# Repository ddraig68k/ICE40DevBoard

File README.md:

# Lattice ICE40HX8K Development board

Intended as a development system for a software CPU computer design.

Includes:
16-bit VGA video
Audio output
512KB SRAM
FT232H interface for UART and device programming
MicroSD card
PS/2 Keyboard and mouse
Sega Megadrive joystick interface
3 push buttons
3 user LEDs
2 seven segment LEDs

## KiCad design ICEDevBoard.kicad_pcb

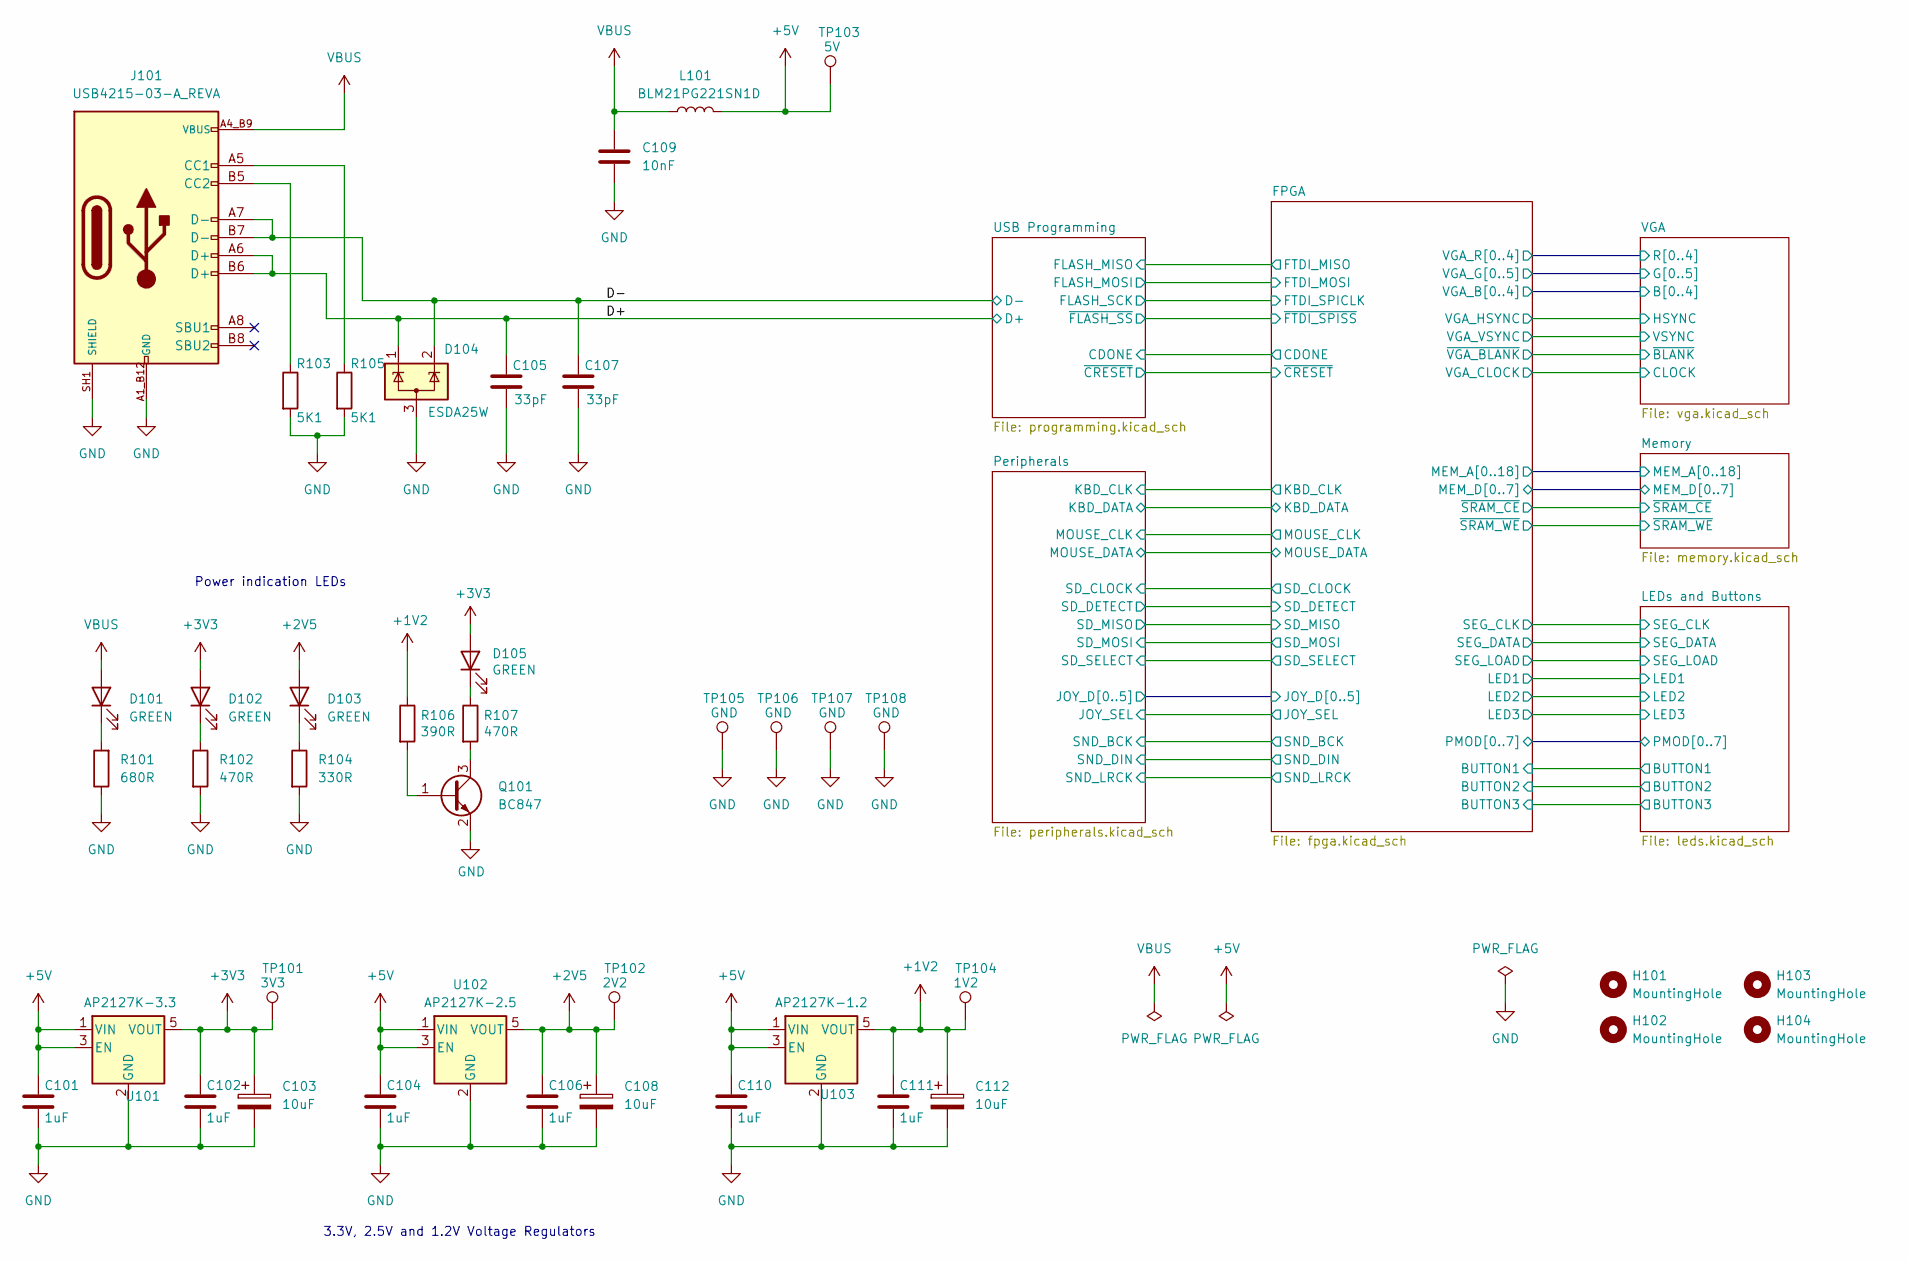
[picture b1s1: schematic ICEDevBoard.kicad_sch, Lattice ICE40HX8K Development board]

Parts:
C101, C102, C104, C106, C110, C111: 1uF; C_0805_2012Metric
C103, C108, C112: 10uF; CP_Elec_4x5.3
C105, C107: 33pF; C_0805_2012Metric
C109: 10nF; C_0805_2012Metric
D101, D102, D103, D105: GREEN; LED_1206_3216Metric
D104: ESDA25W; SOT-23-3
H101, H102, H103, H104: MountingHole; MountingHole_4.3mm_M4
J101: USB4215-03-A_REVA; GCT_USB4215-03-A_REVA; PARTREV A
L101: BLM21PG221SN1D; L_1206_3216Metric
Q101: BC847; SOT-23
R101: 680R; R_0805_2012Metric
R102, R107: 470R; R_0805_2012Metric
R103, R105: 5K1; R_0805_2012Metric
R104: 330R; R_0805_2012Metric
R106: 390R; R_0805_2012Metric
TP101: 3V3; TestPoint_Pad_D1.0mm
TP102: 2V2; TestPoint_Pad_D1.0mm
TP103: 5V; TestPoint_Pad_D1.0mm
TP104: 1V2; TestPoint_Pad_D1.0mm
TP105, TP106, TP107, TP108: GND; TestPoint_THTPad_D1.0mm_Drill0.5mm
U101: AP2127K-3.3; SOT-23-5
U102: AP2127K-2.5; SOT-23-5
U103: AP2127K-1.2; SOT-23-5

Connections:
+1V2: C111.1, C112.1, R106.1, TP104.1, U103.5 (VOUT); also elsewhere on the board
+2V5: C106.1, C108.1, D103.2 (A), TP102.1, U102.5 (VOUT); also elsewhere on the board
+3V3: C102.1, C103.1, D102.2 (A), D105.2 (A), TP101.1, U101.5 (VOUT); also elsewhere on the board
+5V: C101.1, C104.1, C110.1, L101.2, TP103.1, U101.1 (VIN), U101.3 (EN), U102.1 (VIN), U102.3 (EN), U103.1 (VIN), U103.3 (EN); also elsewhere on the board
/D+: C105.1, D104.1 (K), J101.A6 (D+), J101.B6 (D+); also elsewhere on the board
/D-: C107.1, D104.2 (K), J101.A7 (D-), J101.B7 (D-); also elsewhere on the board
GND: C101.2, C102.2, C103.2, C104.2, C105.2, C106.2, C107.2, C108.2, C109.2, C110.2, C111.2, C112.2, D104.3 (A), J101.A1_B12 (GND), J101.B1_A12 (GND), J101.SH1 (SHIELD), J101.SH2 (SHIELD), J101.SH3 (SHIELD), J101.SH4 (SHIELD), Q101.2 (E), R101.1, R102.2, R103.2, R104.2, R105.2, TP105.1, TP106.1, TP107.1, TP108.1, U101.2 (GND), U102.2 (GND), U103.2 (GND); also elsewhere on the board
unnamed: D101.1 (K), R101.2
unnamed: D102.1 (K), R102.1
unnamed: D103.1 (K), R104.1
unnamed: D105.1 (K), R107.1
unnamed: J101.A5 (CC1), R105.1
unnamed: J101.B5 (CC2), R103.1
unnamed: Q101.1 (B), R106.2
unnamed: Q101.3 (C), R107.2
VBUS: C109.1, D101.2 (A), J101.A4_B9 (VBUS), J101.B4_A9 (VBUS), L101.1

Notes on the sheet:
Power indication LEDs
3.3V, 2.5V and 1.2V Voltage Regulators

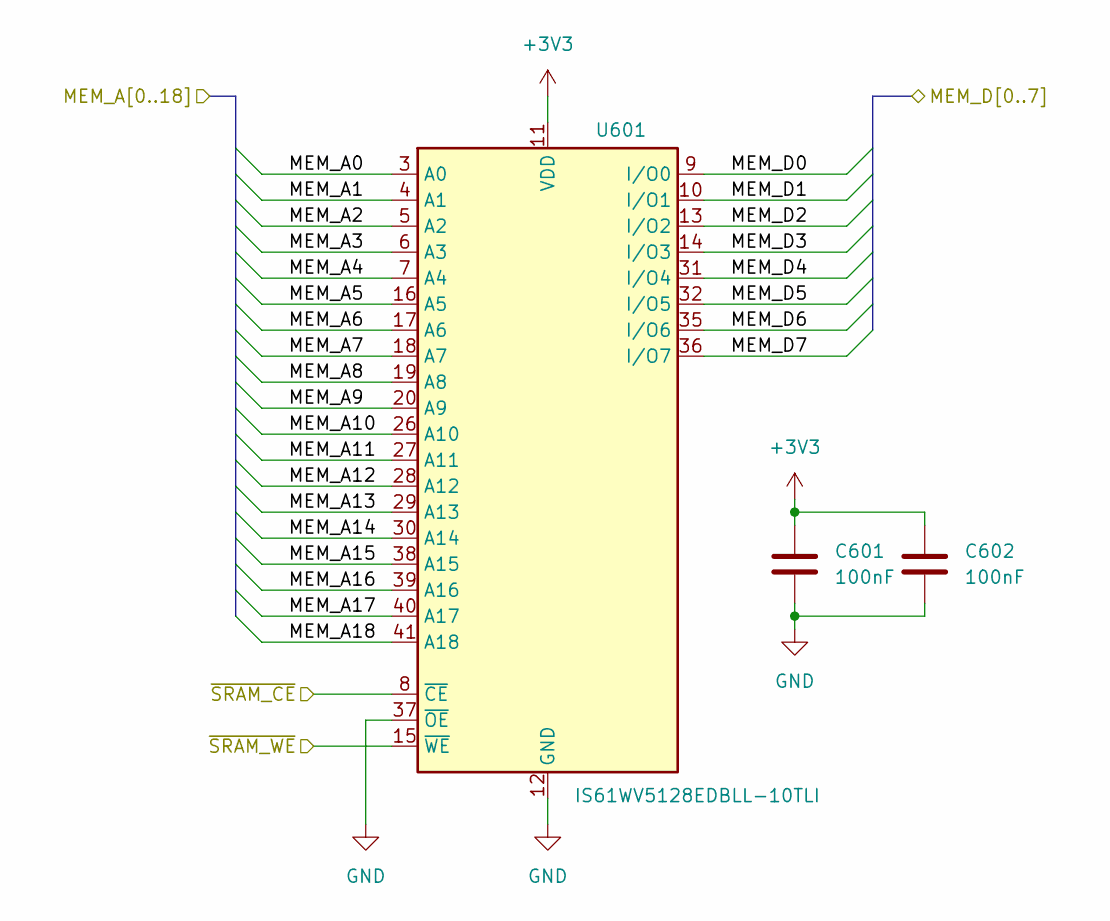
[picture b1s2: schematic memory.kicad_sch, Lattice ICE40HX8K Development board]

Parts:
C601, C602: 100nF; C_0805_2012Metric
U601: IS61WV5128EDBLL-10TLI; TSOP-II-44_10.16x18.41mm_P0.8mm

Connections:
+3V3: C601.1, C602.1, U601.11 (VDD), U601.33 (VDD); also elsewhere on the board
/FPGA/MEM_A0: U601.3 (A0); also elsewhere on the board
/FPGA/MEM_A1: U601.4 (A1); also elsewhere on the board
/FPGA/MEM_A2: U601.5 (A2); also elsewhere on the board
/FPGA/MEM_A3: U601.6 (A3); also elsewhere on the board
/FPGA/MEM_A4: U601.7 (A4); also elsewhere on the board
/FPGA/MEM_A5: U601.16 (A5); also elsewhere on the board
/FPGA/MEM_A6: U601.17 (A6); also elsewhere on the board
/FPGA/MEM_A7: U601.18 (A7); also elsewhere on the board
/FPGA/MEM_A8: U601.19 (A8); also elsewhere on the board
/FPGA/MEM_A9: U601.20 (A9); also elsewhere on the board
/FPGA/MEM_A10: U601.26 (A10); also elsewhere on the board
/FPGA/MEM_A11: U601.27 (A11); also elsewhere on the board
/FPGA/MEM_A12: U601.28 (A12); also elsewhere on the board
/FPGA/MEM_A13: U601.29 (A13); also elsewhere on the board
/FPGA/MEM_A14: U601.30 (A14); also elsewhere on the board
/FPGA/MEM_A15: U601.38 (A15); also elsewhere on the board
/FPGA/MEM_A16: U601.39 (A16); also elsewhere on the board
/FPGA/MEM_A17: U601.40 (A17); also elsewhere on the board
/FPGA/MEM_A18: U601.41 (A18); also elsewhere on the board
/FPGA/MEM_D0: U601.9 (I/O0); also elsewhere on the board
/FPGA/MEM_D1: U601.10 (I/O1); also elsewhere on the board
/FPGA/MEM_D2: U601.13 (I/O2); also elsewhere on the board
/FPGA/MEM_D3: U601.14 (I/O3); also elsewhere on the board
/FPGA/MEM_D4: U601.31 (I/O4); also elsewhere on the board
/FPGA/MEM_D5: U601.32 (I/O5); also elsewhere on the board
/FPGA/MEM_D6: U601.35 (I/O6); also elsewhere on the board
/FPGA/MEM_D7: U601.36 (I/O7); also elsewhere on the board
/FPGA/~SRAM_CE: U601.8 (~CE); also elsewhere on the board
/FPGA/~SRAM_WE: U601.15 (~WE); also elsewhere on the board
GND: C601.2, C602.2, U601.12 (GND), U601.34 (GND), U601.37 (~OE); also elsewhere on the board

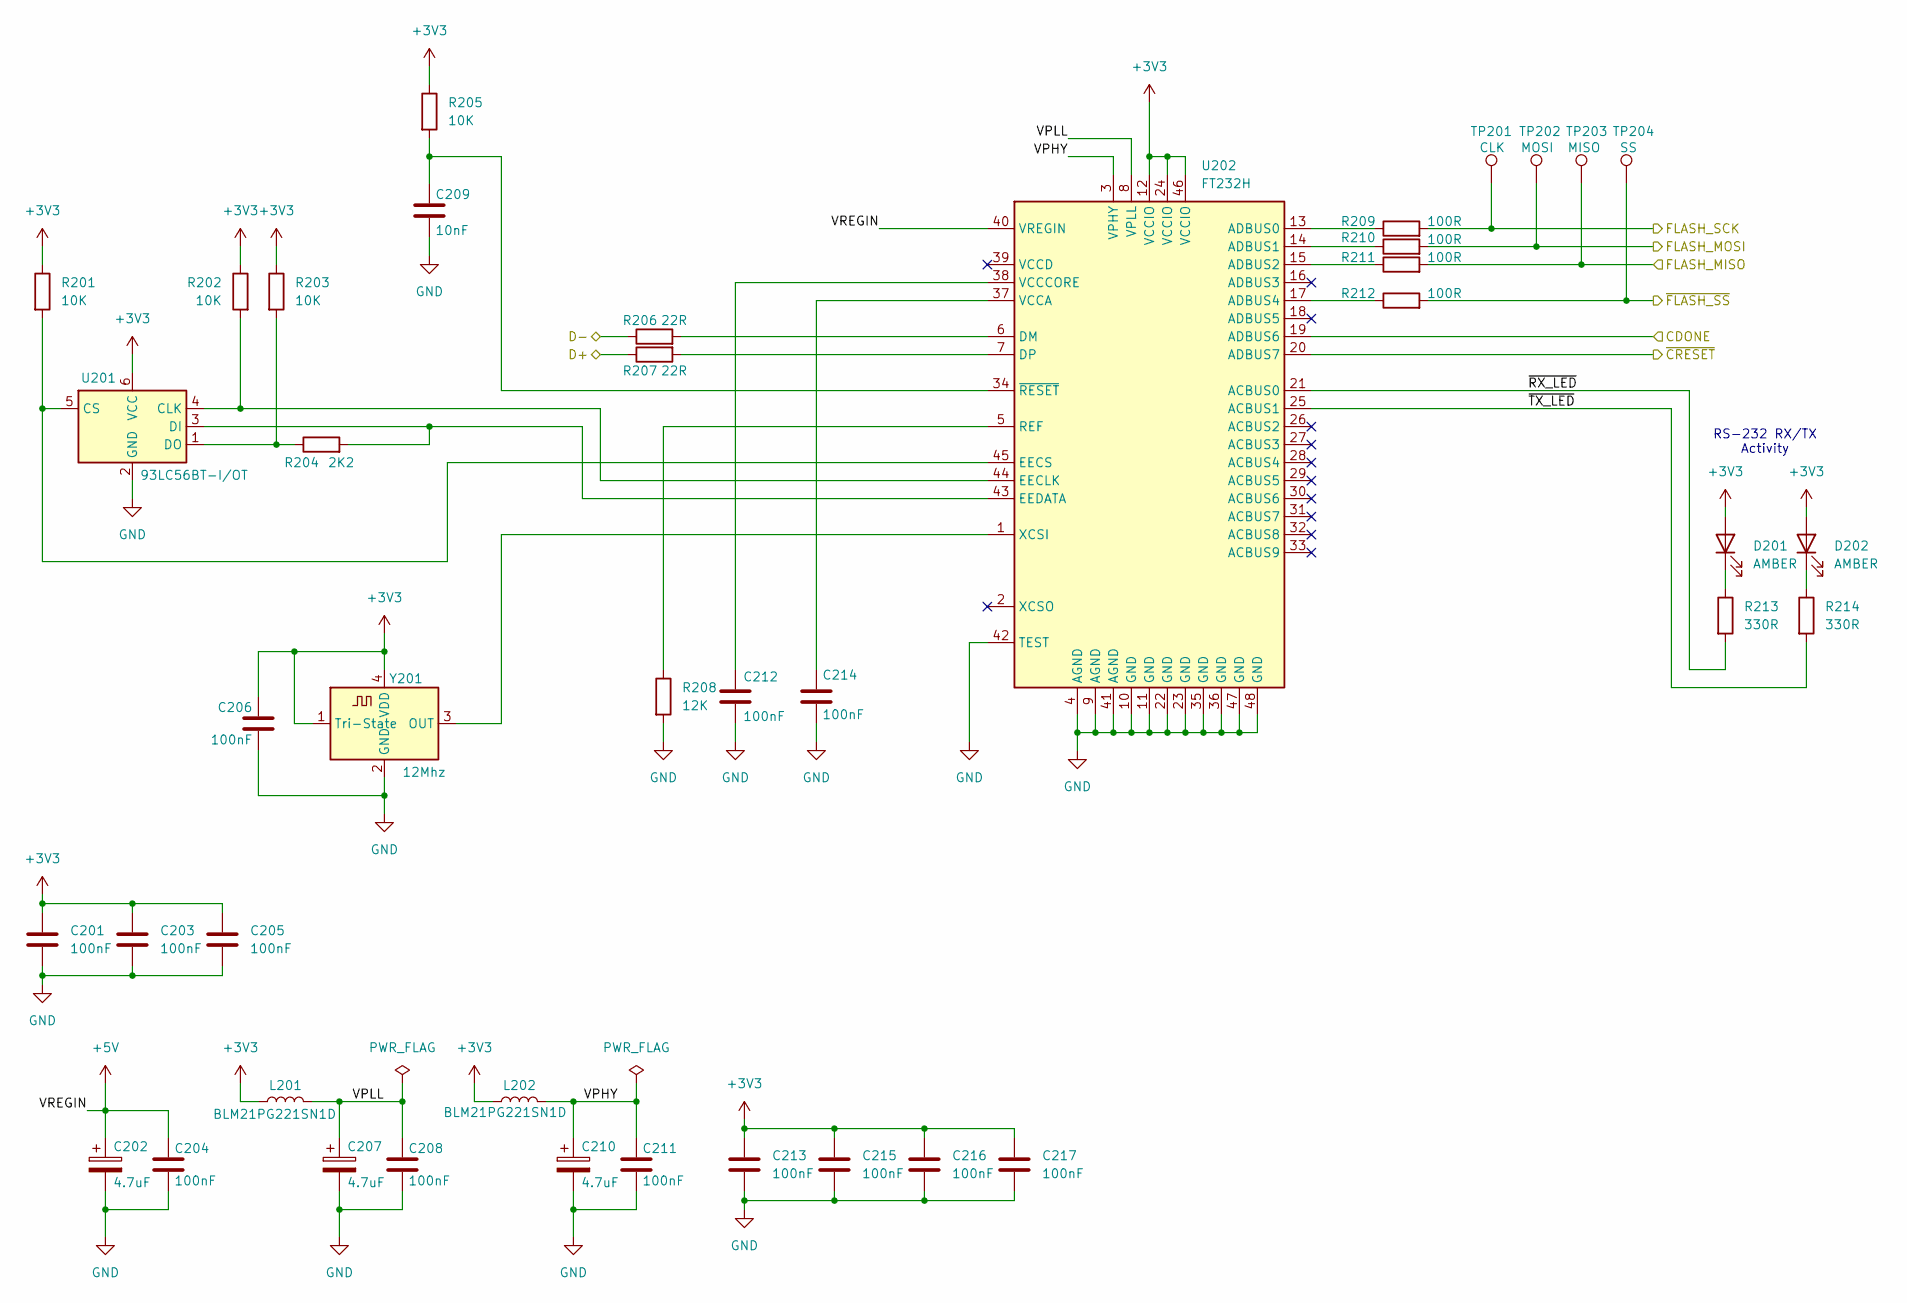
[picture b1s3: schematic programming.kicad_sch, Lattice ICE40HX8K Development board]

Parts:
C201, C203, C204, C205, C206, C208, C211, C212, C213, C214, C215, C216, C217: 100nF; C_0805_2012Metric
C202, C207, C210: 4.7uF; CP_Elec_4x5.3
C209: 10nF; C_0805_2012Metric
D201, D202: AMBER; LED_1206_3216Metric
L201, L202: BLM21PG221SN1D; L_1206_3216Metric
R201, R202, R203, R205: 10K; R_0805_2012Metric
R204: 2K2; R_0805_2012Metric
R206, R207: 22R; R_0805_2012Metric
R208: 12K; R_0805_2012Metric
R209, R210, R211, R212: 100R; R_0805_2012Metric
R213, R214: 330R; R_0805_2012Metric
TP201: CLK; TestPoint_Pad_D1.0mm
TP202: MOSI; TestPoint_Pad_D1.0mm
TP203: MISO; TestPoint_Pad_D1.0mm
TP204: SS; TestPoint_Pad_D1.0mm
U201: 93LC56BT-I/OT; SOT-23-6
U202: FT232H; LQFP-48_7x7mm_P0.5mm
Y201: 12Mhz; Oscillator_SMD_ECS_2520MV-xxx-xx-4Pin_2.5x2.0mm

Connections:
+3V3: C201.1, C203.1, C205.1, C206.1, C213.1, C215.1, C216.1, C217.1, D201.2 (A), D202.2 (A), L201.1, L202.1, R201.1, R202.1, R203.1, R205.1, U201.6 (VCC), U202.12 (VCCIO), U202.24 (VCCIO), U202.46 (VCCIO), Y201.1 (Tri-State), Y201.4 (VDD); also elsewhere on the board
+5V: C202.1, C204.1, U202.40 (VREGIN); also elsewhere on the board
/D+: R207.1; also elsewhere on the board
/D-: R206.1; also elsewhere on the board
/FPGA/CDONE: U202.19 (ADBUS6); also elsewhere on the board
/FPGA/FTDI_MISO: R211.2, TP203.1; also elsewhere on the board
/FPGA/FTDI_MOSI: R210.2, TP202.1; also elsewhere on the board
/FPGA/FTDI_SPICLK: R209.2, TP201.1; also elsewhere on the board
/FPGA/~CRESET: U202.20 (ADBUS7); also elsewhere on the board
/FPGA/~FTDI_SPISS: R212.2, TP204.1; also elsewhere on the board
/USB Programming/VPHY: C210.1, C211.1, L202.2, U202.3 (VPHY)
/USB Programming/VPLL: C207.1, C208.1, L201.2, U202.8 (VPLL)
/USB Programming/~RX_LED: R213.2, U202.21 (ACBUS0)
/USB Programming/~TX_LED: R214.2, U202.25 (ACBUS1)
GND: C201.2, C202.2, C203.2, C204.2, C205.2, C206.2, C207.2, C208.2, C209.2, C210.2, C211.2, C212.2, C213.2, C214.2, C215.2, C216.2, C217.2, R208.2, U201.2 (GND), U202.4 (AGND), U202.9 (AGND), U202.10 (GND), U202.11 (GND), U202.22 (GND), U202.23 (GND), U202.35 (GND), U202.36 (GND), U202.41 (AGND), U202.42 (TEST), U202.47 (GND), U202.48 (GND), Y201.2 (GND); also elsewhere on the board
unnamed: D201.1 (K), R213.1
unnamed: D202.1 (K), R214.1
unnamed: R202.2, U201.4 (CLK), U202.44 (EECLK)
unnamed: R201.2, U201.5 (CS), U202.45 (EECS)
unnamed: R204.2, U201.3 (DI), U202.43 (EEDATA)
unnamed: R203.2, R204.1, U201.1 (DO)
unnamed: R209.1, U202.13 (ADBUS0)
unnamed: R210.1, U202.14 (ADBUS1)
unnamed: R211.1, U202.15 (ADBUS2)
unnamed: R212.1, U202.17 (ADBUS4)
unnamed: R206.2, U202.6 (DM)
unnamed: R207.2, U202.7 (DP)
unnamed: R208.1, U202.5 (REF)
unnamed: C214.1, U202.37 (VCCA)
unnamed: C212.1, U202.38 (VCCCORE)
unnamed: U202.1 (XCSI), Y201.3 (OUT)
unnamed: C209.1, R205.2, U202.34 (~RESET)

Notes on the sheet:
RS-232 RX/TX Activity

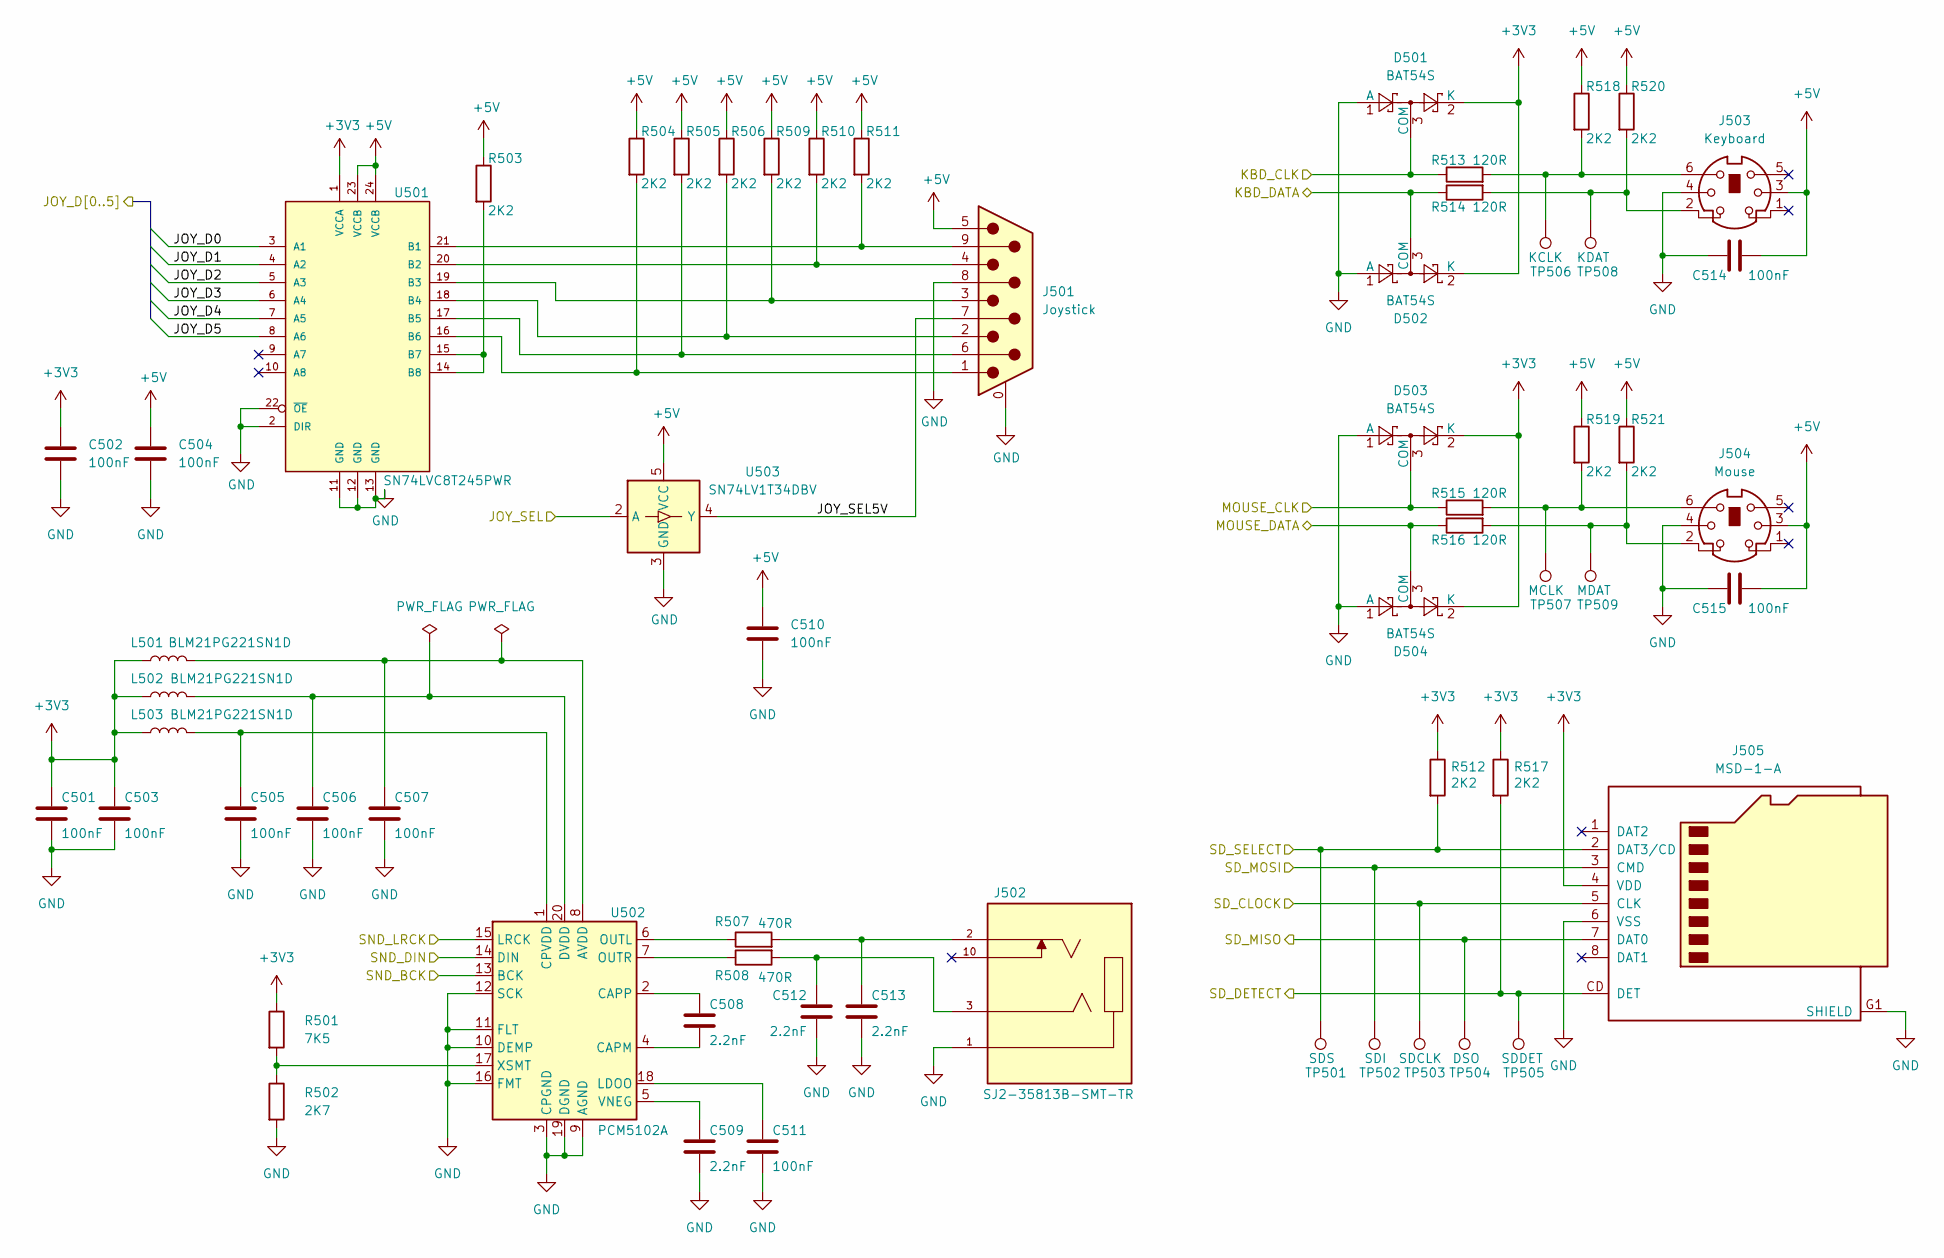
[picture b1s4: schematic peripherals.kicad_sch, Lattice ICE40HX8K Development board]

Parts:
C501, C502, C503, C504, C505, C506, C507, C510, C511, C514, C515: 100nF; C_0805_2012Metric
C508, C509, C512, C513: 2.2nF; C_0805_2012Metric
D501, D502, D503, D504: BAT54S; SOT-23
J501: Joystick; DSUB-9_Pins_Horizontal_P2.77x2.84mm_EdgePinOffset4.94mm_Hou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
J502: SJ2-35813B-SMT-TR; CUI_SJ2-35813B-SMT-TR
J503: Keyboard; MINI-DIN-6-FULL-SHIELD
J504: Mouse; MINI-DIN-6-FULL-SHIELD
J505: MSD-1-A; CUI_MSD-1-A
L501, L502, L503: BLM21PG221SN1D; L_1206_3216Metric
R501: 7K5; R_0805_2012Metric
R502: 2K7; R_0805_2012Metric
R503, R504, R505, R506, R509, R510, R511, R512, R517, R518, R519, R520, R521: 2K2; R_0805_2012Metric
R507, R508: 470R; R_0805_2012Metric
R513, R514, R515, R516: 120R; R_0805_2012Metric
TP501: SDS; TestPoint_Pad_D1.0mm
TP502: SDI; TestPoint_Pad_D1.0mm
TP503: SDCLK; TestPoint_Pad_D1.0mm
TP504: DSO; TestPoint_Pad_D1.0mm
TP505: SDDET; TestPoint_Pad_D1.0mm
TP506: KCLK; TestPoint_Pad_D1.0mm
TP507: MCLK; TestPoint_Pad_D1.0mm
TP508: KDAT; TestPoint_Pad_D1.0mm
TP509: MDAT; TestPoint_Pad_D1.0mm
U501: SN74LVC8T245PWR; SOP65P640X120-24N
U502: PCM5102A; TSSOP-20_4.4x6.5mm_P0.65mm
U503: SN74LV1T34DBV; SOT-23-5

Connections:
+3V3: C501.1, C502.1, C503.1, D501.2 (K), D502.2 (K), D503.2 (K), D504.2 (K), J505.4 (VDD), L501.1, L502.1, L503.1, R501.1, R512.1, R517.1, U501.1 (VCCA); also elsewhere on the board
+5V: C504.1, C510.1, C514.2, C515.2, J501.5, J503.3, J504.3, R503.1, R504.1, R505.1, R506.1, R509.1, R510.1, R511.1, R518.1, R519.1, R520.1, R521.1, U501.23 (VCCB), U501.24 (VCCB), U503.5 (VCC); also elsewhere on the board
/FPGA/JOY_D0: U501.3 (A1); also elsewhere on the board
/FPGA/JOY_D1: U501.4 (A2); also elsewhere on the board
/FPGA/JOY_D2: U501.5 (A3); also elsewhere on the board
/FPGA/JOY_D3: U501.6 (A4); also elsewhere on the board
/FPGA/JOY_D4: U501.7 (A5); also elsewhere on the board
/FPGA/JOY_D5: U501.8 (A6); also elsewhere on the board
/FPGA/JOY_SEL: U503.2 (A); also elsewhere on the board
/FPGA/KBD_CLK: D501.3 (COM), R513.1; also elsewhere on the board
/FPGA/KBD_DATA: D502.3 (COM), R514.1; also elsewhere on the board
/FPGA/MOUSE_CLK: D503.3 (COM), R515.1; also elsewhere on the board
/FPGA/MOUSE_DATA: D504.3 (COM), R516.1; also elsewhere on the board
/FPGA/SD_CLOCK: J505.5 (CLK), TP503.1; also elsewhere on the board
/FPGA/SD_DETECT: J505.CD (DET), R517.2, TP505.1; also elsewhere on the board
/FPGA/SD_MISO: J505.7 (DAT0), TP504.1; also elsewhere on the board
/FPGA/SD_MOSI: J505.3 (CMD), TP502.1; also elsewhere on the board
/FPGA/SD_SELECT: J505.2 (DAT3/CD), R512.2, TP501.1; also elsewhere on the board
/FPGA/SND_BCK: U502.13 (BCK); also elsewhere on the board
/FPGA/SND_DIN: U502.14 (DIN); also elsewhere on the board
/FPGA/SND_LRCK: U502.15 (LRCK); also elsewhere on the board
/Peripherals/JOY_SEL5V: J501.7, U503.4 (Y)
GND: C501.2, C502.2, C503.2, C504.2, C505.2, C506.2, C507.2, C509.2, C510.2, C511.2, C512.2, C513.2, C514.1, C515.1, D501.1 (A), D502.1 (A), D503.1 (A), D504.1 (A), J501.0 (PAD), J501.8, J502.1, J503.4, J504.4, J505.6 (VSS), J505.G1 (SHIELD), J505.G2 (SHIELD), J505.G3 (SHIELD), J505.G4 (SHIELD), R502.2, U501.2 (DIR), U501.11 (GND), U501.12 (GND), U501.13 (GND), U501.22 (~OE), U502.3 (CPGND), U502.9 (AGND), U502.10 (DEMP), U502.11 (FLT), U502.12 (SCK), U502.16 (FMT), U502.19 (DGND), U503.3 (GND); also elsewhere on the board
unnamed: C512.1, J502.3, R508.2
unnamed: C513.1, J502.2, R507.2
unnamed: J503.2, R514.2, R520.2, TP508.1
unnamed: J503.6, R513.2, R518.2, TP506.1
unnamed: J504.2, R516.2, R521.2, TP509.1
unnamed: J504.6, R515.2, R519.2, TP507.1
unnamed: J501.9, R511.2, U501.21 (B1)
unnamed: J501.4, R510.2, U501.20 (B2)
unnamed: J501.3, R509.2, U501.19 (B3)
unnamed: J501.2, R506.2, U501.18 (B4)
unnamed: J501.6, R505.2, U501.17 (B5)
unnamed: J501.1, R504.2, U501.16 (B6)
unnamed: R503.2, U501.14 (B8), U501.15 (B7)
unnamed: C507.1, L501.2, U502.8 (AVDD)
unnamed: C508.2, U502.4 (CAPM)
unnamed: C508.1, U502.2 (CAPP)
unnamed: C505.1, L503.2, U502.1 (CPVDD)
unnamed: C506.1, L502.2, U502.20 (DVDD)
unnamed: C511.1, U502.18 (LDOO)
unnamed: R507.1, U502.6 (OUTL)
unnamed: R508.1, U502.7 (OUTR)
unnamed: C509.1, U502.5 (VNEG)
unnamed: R501.2, R502.1, U502.17 (XSMT)

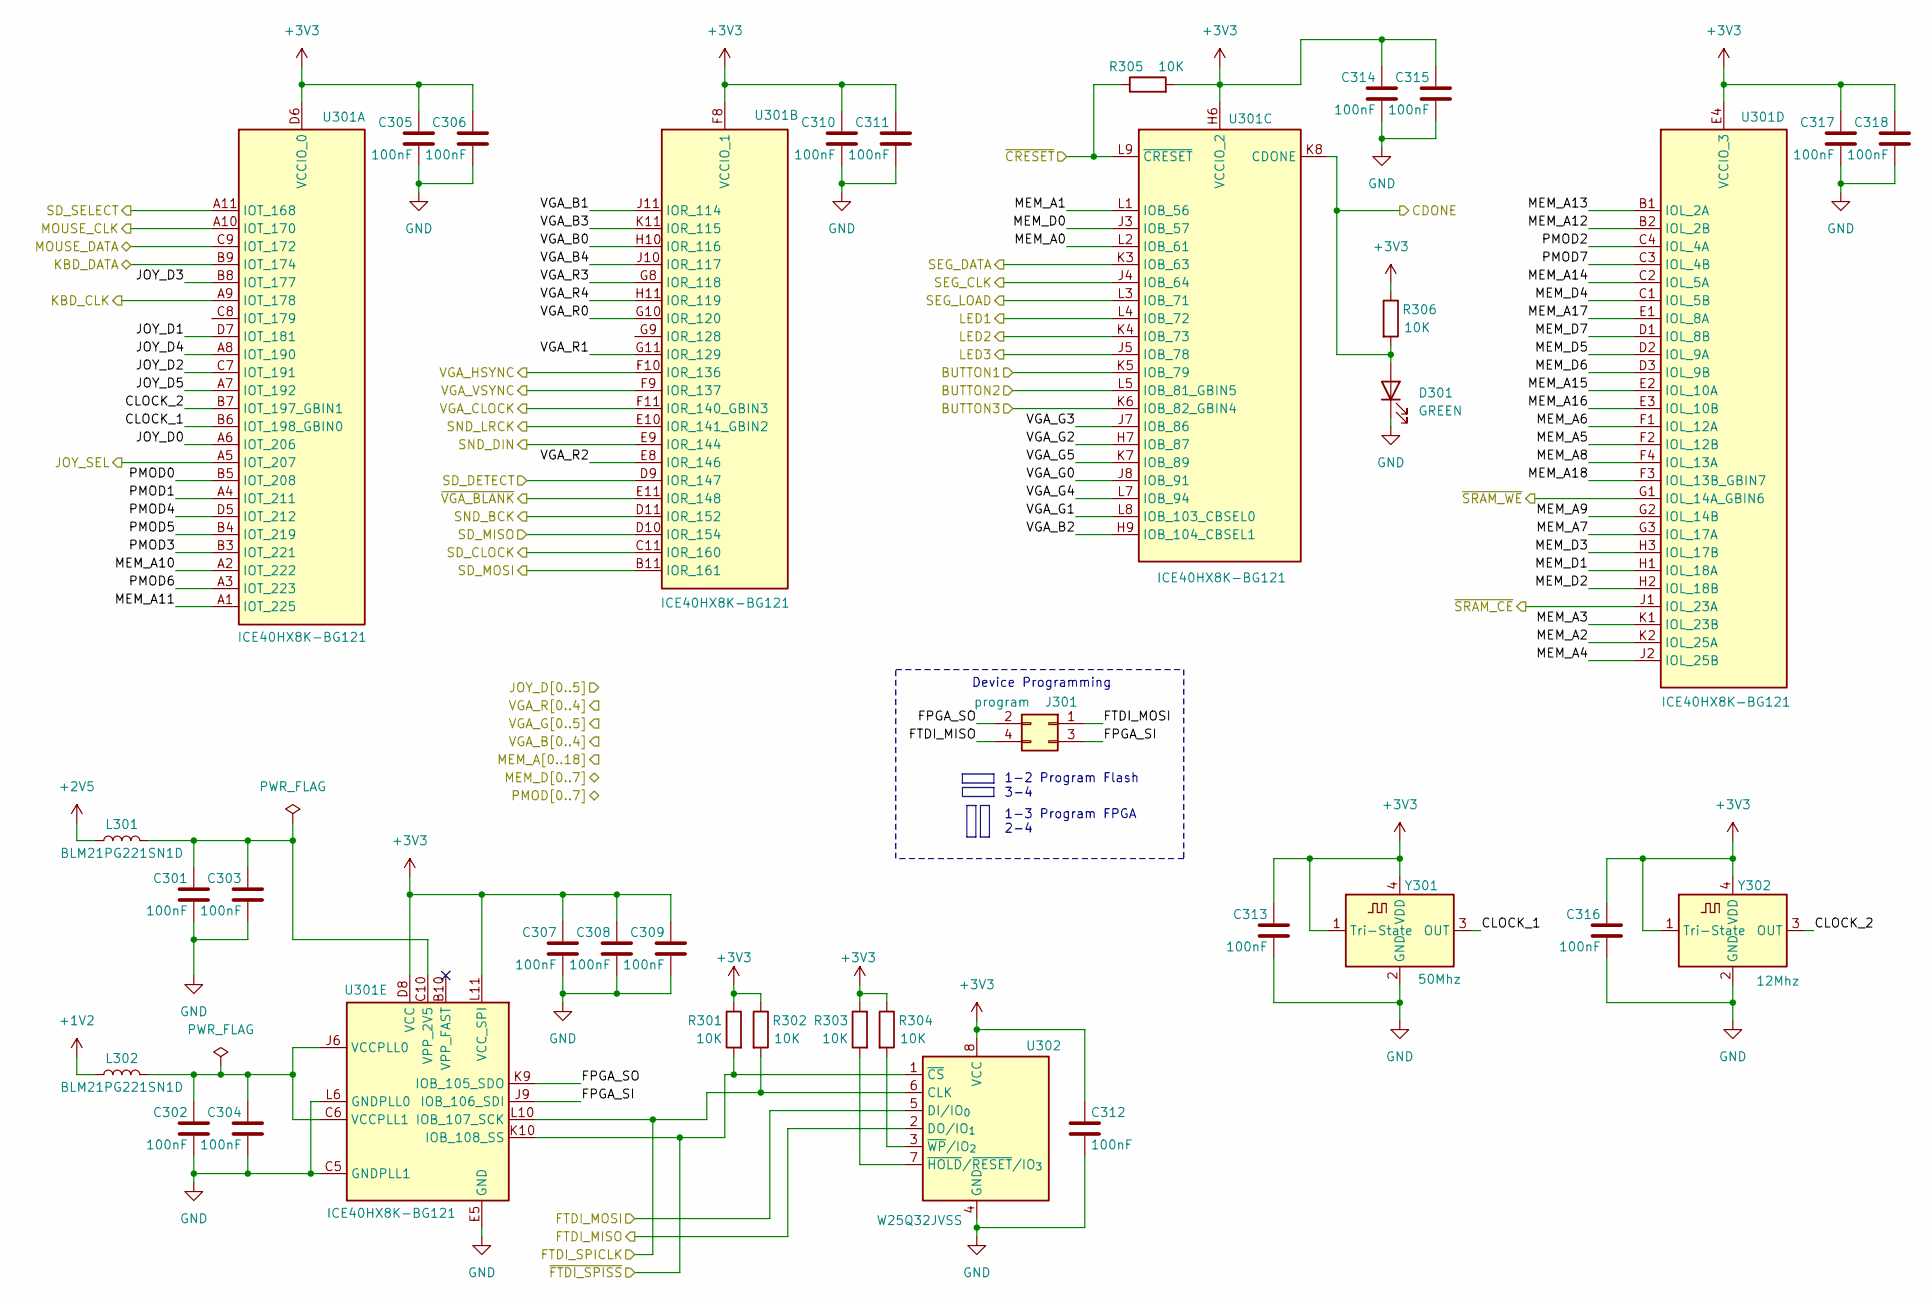
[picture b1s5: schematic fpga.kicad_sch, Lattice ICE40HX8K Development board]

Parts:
C301, C302, C303, C304, C305, C306, C307, C308, C309, C310, C311, C312, C313, C314, C315, C316, C317, C318: 100nF; C_0603_1608Metric
D301: GREEN; LED_1206_3216Metric
J301: program; PinSocket_2x02_P2.54mm_Vertical
L301, L302: BLM21PG221SN1D; L_1206_3216Metric
R301, R302, R303, R304, R305, R306: 10K; R_0805_2012Metric
U301: ICE40HX8K-BG121; BGA-121_9.0x9.0mm_Layout11x11_P0.8mm_Ball0.4mm_Pad0.35mm_NS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
U302: W25Q32JVSS; SOIC-8_5.3x5.3mm_P1.27mm
Y301: 50Mhz; Oscillator_SMD_ECS_2520MV-xxx-xx-4Pin_2.5x2.0mm
Y302: 12Mhz; Oscillator_SMD_ECS_2520MV-xxx-xx-4Pin_2.5x2.0mm

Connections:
+1V2: L302.1; also elsewhere on the board
+2V5: L301.1; also elsewhere on the board
+3V3: C305.1, C306.1, C307.1, C308.1, C309.1, C310.1, C311.1, C312.1, C313.1, C314.1, C315.1, C316.1, C317.1, C318.1, R301.1, R302.1, R303.1, R304.1, R305.2, R306.1, U301.D4 (VCC), U301.D6 (VCCIO_0), U301.D8 (VCC), U301.E4 (VCCIO_3), U301.F8 (VCCIO_1), U301.G4 (VCCIO_3), U301.H4 (VCC), U301.H6 (VCCIO_2), U301.H8 (VCC), U301.L11 (VCC_SPI), U302.8 (VCC), Y301.1 (Tri-State), Y301.4 (VDD), Y302.1 (Tri-State), Y302.4 (VDD); also elsewhere on the board
/FPGA/BUTTON1: U301.K5 (IOB_79); also elsewhere on the board
/FPGA/BUTTON2: U301.L5 (IOB_81_GBIN5); also elsewhere on the board
/FPGA/BUTTON3: U301.K6 (IOB_82_GBIN4); also elsewhere on the board
/FPGA/CDONE: D301.2 (A), R306.2, U301.K8 (CDONE); also elsewhere on the board
/FPGA/CLOCK_1: U301.B6 (IOT_198_GBIN0), Y301.3 (OUT)
/FPGA/CLOCK_2: U301.B7 (IOT_197_GBIN1), Y302.3 (OUT)
/FPGA/FPGA_SI: J301.3, U301.J9 (IOB_106_SDI)
/FPGA/FPGA_SO: J301.2, U301.K9 (IOB_105_SDO)
/FPGA/FTDI_MISO: J301.4, U302.2 (DO/IO_{1}); also elsewhere on the board
/FPGA/FTDI_MOSI: J301.1, U302.5 (DI/IO_{0}); also elsewhere on the board
/FPGA/FTDI_SPICLK: R302.2, U301.L10 (IOB_107_SCK), U302.6 (CLK); also elsewhere on the board
/FPGA/JOY_D0: U301.A6 (IOT_206); also elsewhere on the board
/FPGA/JOY_D1: U301.D7 (IOT_181); also elsewhere on the board
/FPGA/JOY_D2: U301.C7 (IOT_191); also elsewhere on the board
/FPGA/JOY_D3: U301.B8 (IOT_177); also elsewhere on the board
/FPGA/JOY_D4: U301.A8 (IOT_190); also elsewhere on the board
/FPGA/JOY_D5: U301.A7 (IOT_192); also elsewhere on the board
/FPGA/JOY_SEL: U301.A5 (IOT_207); also elsewhere on the board
/FPGA/KBD_CLK: U301.A9 (IOT_178); also elsewhere on the board
/FPGA/KBD_DATA: U301.B9 (IOT_174); also elsewhere on the board
/FPGA/LED1: U301.L4 (IOB_72); also elsewhere on the board
/FPGA/LED2: U301.K4 (IOB_73); also elsewhere on the board
/FPGA/LED3: U301.J5 (IOB_78); also elsewhere on the board
/FPGA/MEM_A0: U301.L2 (IOB_61); also elsewhere on the board
/FPGA/MEM_A1: U301.L1 (IOB_56); also elsewhere on the board
/FPGA/MEM_A2: U301.K2 (IOL_25A); also elsewhere on the board
/FPGA/MEM_A3: U301.K1 (IOL_23B); also elsewhere on the board
/FPGA/MEM_A4: U301.J2 (IOL_25B); also elsewhere on the board
/FPGA/MEM_A5: U301.F2 (IOL_12B); also elsewhere on the board
/FPGA/MEM_A6: U301.F1 (IOL_12A); also elsewhere on the board
/FPGA/MEM_A7: U301.G3 (IOL_17A); also elsewhere on the board
/FPGA/MEM_A8: U301.F4 (IOL_13A); also elsewhere on the board
/FPGA/MEM_A9: U301.G2 (IOL_14B); also elsewhere on the board
/FPGA/MEM_A10: U301.A2 (IOT_222); also elsewhere on the board
/FPGA/MEM_A11: U301.A1 (IOT_225); also elsewhere on the board
/FPGA/MEM_A12: U301.B2 (IOL_2B); also elsewhere on the board
/FPGA/MEM_A13: U301.B1 (IOL_2A); also elsewhere on the board
/FPGA/MEM_A14: U301.C2 (IOL_5A); also elsewhere on the board
/FPGA/MEM_A15: U301.E2 (IOL_10A); also elsewhere on the board
/FPGA/MEM_A16: U301.E3 (IOL_10B); also elsewhere on the board
/FPGA/MEM_A17: U301.E1 (IOL_8A); also elsewhere on the board
/FPGA/MEM_A18: U301.F3 (IOL_13B_GBIN7); also elsewhere on the board
/FPGA/MEM_D0: U301.J3 (IOB_57); also elsewhere on the board
/FPGA/MEM_D1: U301.H1 (IOL_18A); also elsewhere on the board
/FPGA/MEM_D2: U301.H2 (IOL_18B); also elsewhere on the board
/FPGA/MEM_D3: U301.H3 (IOL_17B); also elsewhere on the board
/FPGA/MEM_D4: U301.C1 (IOL_5B); also elsewhere on the board
/FPGA/MEM_D5: U301.D2 (IOL_9A); also elsewhere on the board
/FPGA/MEM_D6: U301.D3 (IOL_9B); also elsewhere on the board
/FPGA/MEM_D7: U301.D1 (IOL_8B); also elsewhere on the board
/FPGA/MOUSE_CLK: U301.A10 (IOT_170); also elsewhere on the board
/FPGA/MOUSE_DATA: U301.C9 (IOT_172); also elsewhere on the board
/FPGA/PMOD0: U301.B5 (IOT_208); also elsewhere on the board
/FPGA/PMOD1: U301.A4 (IOT_211); also elsewhere on the board
/FPGA/PMOD2: U301.C4 (IOL_4A); also elsewhere on the board
/FPGA/PMOD3: U301.B3 (IOT_221); also elsewhere on the board
/FPGA/PMOD4: U301.D5 (IOT_212); also elsewhere on the board
/FPGA/PMOD5: U301.B4 (IOT_219); also elsewhere on the board
/FPGA/PMOD6: U301.A3 (IOT_223); also elsewhere on the board
/FPGA/PMOD7: U301.C3 (IOL_4B); also elsewhere on the board
/FPGA/SD_CLOCK: U301.C11 (IOR_160); also elsewhere on the board
/FPGA/SD_DETECT: U301.D9 (IOR_147); also elsewhere on the board
/FPGA/SD_MISO: U301.D10 (IOR_154); also elsewhere on the board
/FPGA/SD_MOSI: U301.B11 (IOR_161); also elsewhere on the board
/FPGA/SD_SELECT: U301.A11 (IOT_168); also elsewhere on the board
/FPGA/SEG_CLK: U301.J4 (IOB_64); also elsewhere on the board
/FPGA/SEG_DATA: U301.K3 (IOB_63); also elsewhere on the board
/FPGA/SEG_LOAD: U301.L3 (IOB_71); also elsewhere on the board
/FPGA/SND_BCK: U301.D11 (IOR_152); also elsewhere on the board
/FPGA/SND_DIN: U301.E9 (IOR_144); also elsewhere on the board
/FPGA/SND_LRCK: U301.E10 (IOR_141_GBIN2); also elsewhere on the board
/FPGA/VGA_B0: U301.H10 (IOR_116); also elsewhere on the board
/FPGA/VGA_B1: U301.J11 (IOR_114); also elsewhere on the board
/FPGA/VGA_B2: U301.H9 (IOB_104_CBSEL1); also elsewhere on the board
/FPGA/VGA_B3: U301.K11 (IOR_115); also elsewhere on the board
/FPGA/VGA_B4: U301.J10 (IOR_117); also elsewhere on the board
/FPGA/VGA_CLOCK: U301.F11 (IOR_140_GBIN3); also elsewhere on the board
/FPGA/VGA_G0: U301.J8 (IOB_91); also elsewhere on the board
/FPGA/VGA_G1: U301.L8 (IOB_103_CBSEL0); also elsewhere on the board
/FPGA/VGA_G2: U301.H7 (IOB_87); also elsewhere on the board
/FPGA/VGA_G3: U301.J7 (IOB_86); also elsewhere on the board
/FPGA/VGA_G4: U301.L7 (IOB_94); also elsewhere on the board
/FPGA/VGA_G5: U301.K7 (IOB_89); also elsewhere on the board
/FPGA/VGA_HSYNC: U301.F10 (IOR_136); also elsewhere on the board
/FPGA/VGA_R0: U301.G10 (IOR_120); also elsewhere on the board
/FPGA/VGA_R1: U301.G11 (IOR_129); also elsewhere on the board
/FPGA/VGA_R2: U301.E8 (IOR_146); also elsewhere on the board
/FPGA/VGA_R3: U301.G8 (IOR_118); also elsewhere on the board
/FPGA/VGA_R4: U301.H11 (IOR_119); also elsewhere on the board
/FPGA/VGA_VSYNC: U301.F9 (IOR_137); also elsewhere on the board
/FPGA/~CRESET: R305.1, U301.L9 (~CRESET); also elsewhere on the board
/FPGA/~FTDI_SPISS: R301.2, U301.K10 (IOB_108_SS), U302.1 (~CS); also elsewhere on the board
/FPGA/~SRAM_CE: U301.J1 (IOL_23A); also elsewhere on the board
/FPGA/~SRAM_WE: U301.G1 (IOL_14A_GBIN6); also elsewhere on the board
/FPGA/~VGA_BLANK: U301.E11 (IOR_148); also elsewhere on the board
GND: C301.2, C302.2, C303.2, C304.2, C305.2, C306.2, C307.2, C308.2, C309.2, C310.2, C311.2, C312.2, C313.2, C314.2, C315.2, C316.2, C317.2, C318.2, D301.1 (K), U301.C5 (GNDPLL1), U301.E5 (GND), U301.E6 (GND), U301.E7 (GND), U301.F5 (GND), U301.F6 (GND), U301.F7 (GND), U301.G5 (GND), U301.G6 (GND), U301.G7 (GND), U301.H5 (GND), U301.L6 (GNDPLL0), U302.4 (GND), Y301.2 (GND), Y302.2 (GND); also elsewhere on the board
unnamed: C302.1, C304.1, L302.2, U301.C6 (VCCPLL1), U301.J6 (VCCPLL0)
unnamed: C301.1, C303.1, L301.2, U301.C10 (VPP_2V5)
unnamed: R303.2, U302.7 (~HOLD/~RESET/IO_{3})
unnamed: R304.2, U302.3 (~WP/IO_{2})

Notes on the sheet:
1-2 Program Flash 3-4
1-3 Program FPGA 2-4
Device Programming
